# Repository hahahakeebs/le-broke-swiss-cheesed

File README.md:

I saw le broke and said, wow, it'd be really nice with more holes.

none of this is tested, yolo this to jlc at your own risk. I'm not responsible for you burning six dollars or anything that follows from you burning those six dollars.

assuming it works, then there is hotswap compatibility with MX, Choc v1/2, and KS27/33.

upstream readme follows below.

silly wacky split-but-not-split adaptation of le chiffre.

ez to assemble, reversible pcb, face down n!n/pro micro (zmk only!!), requires diodes and 2 6x6 buttons.

WATCH YOUR DIODE ORIENTATION!!! IT MATTERS!

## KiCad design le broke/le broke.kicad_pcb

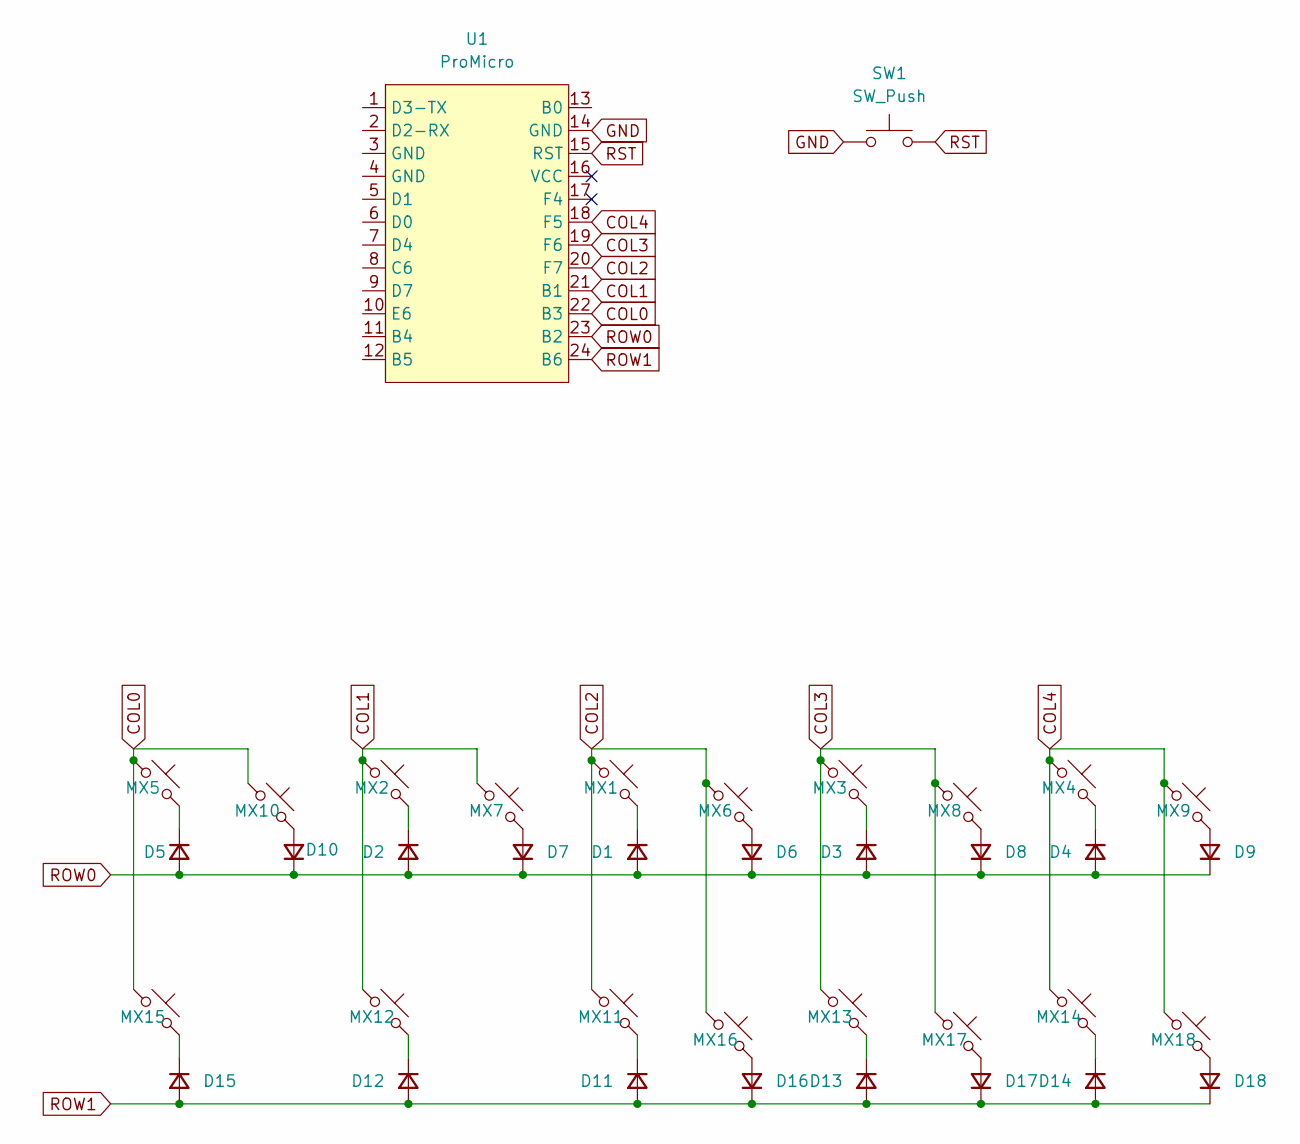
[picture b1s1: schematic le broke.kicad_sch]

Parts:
D1, D2, D3, D4, D5, D6, D7, D8, D9, D10, D11, D12, D13, D14, D15, D16, D17, D18: D_Small; D_A-405_P7.62mm_Horizontal
MX1, MX2, MX3, MX4, MX5, MX6, MX7, MX8, MX9, MX10, MX11, MX12, MX13, MX14, MX15, MX16, MX17, MX18: MX_SW_solder; SW_MX_1u_rev
SW1: SW_Push; SW_PUSH_6mm
U1: ProMicro; ProMicro_Reversible_Single

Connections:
COL0: MX5.1, MX10.1, MX15.1, U1.22 (B3)
COL1: MX2.1, MX7.1, MX12.1, U1.21 (B1)
COL2: MX1.1, MX6.1, MX11.1, MX16.1, U1.20 (F7)
COL3: MX3.1, MX8.1, MX13.1, MX17.1, U1.19 (F6)
COL4: MX4.1, MX9.1, MX14.1, MX18.1, U1.18 (F5)
GND: SW1.1, U1.14 (GND)
unnamed: D1.1 (K), MX1.2
unnamed: D2.1 (K), MX2.2
unnamed: D3.1 (K), MX3.2
unnamed: D4.1 (K), MX4.2
unnamed: D5.1 (K), MX5.2
unnamed: D6.2 (A), MX6.2
unnamed: D7.2 (A), MX7.2
unnamed: D8.2 (A), MX8.2
unnamed: D9.2 (A), MX9.2
unnamed: D10.2 (A), MX10.2
unnamed: D11.1 (K), MX11.2
unnamed: D12.1 (K), MX12.2
unnamed: D13.1 (K), MX13.2
unnamed: D14.1 (K), MX14.2
unnamed: D15.1 (K), MX15.2
unnamed: D16.2 (A), MX16.2
unnamed: D17.2 (A), MX17.2
unnamed: D18.2 (A), MX18.2
ROW0: D1.2 (A), D2.2 (A), D3.2 (A), D4.2 (A), D5.2 (A), D6.1 (K), D7.1 (K), D8.1 (K), D9.1 (K), D10.1 (K), U1.23 (B2)
ROW1: D11.2 (A), D12.2 (A), D13.2 (A), D14.2 (A), D15.2 (A), D16.1 (K), D17.1 (K), D18.1 (K), U1.24 (B6)
RST: SW1.2, U1.15 (RST)

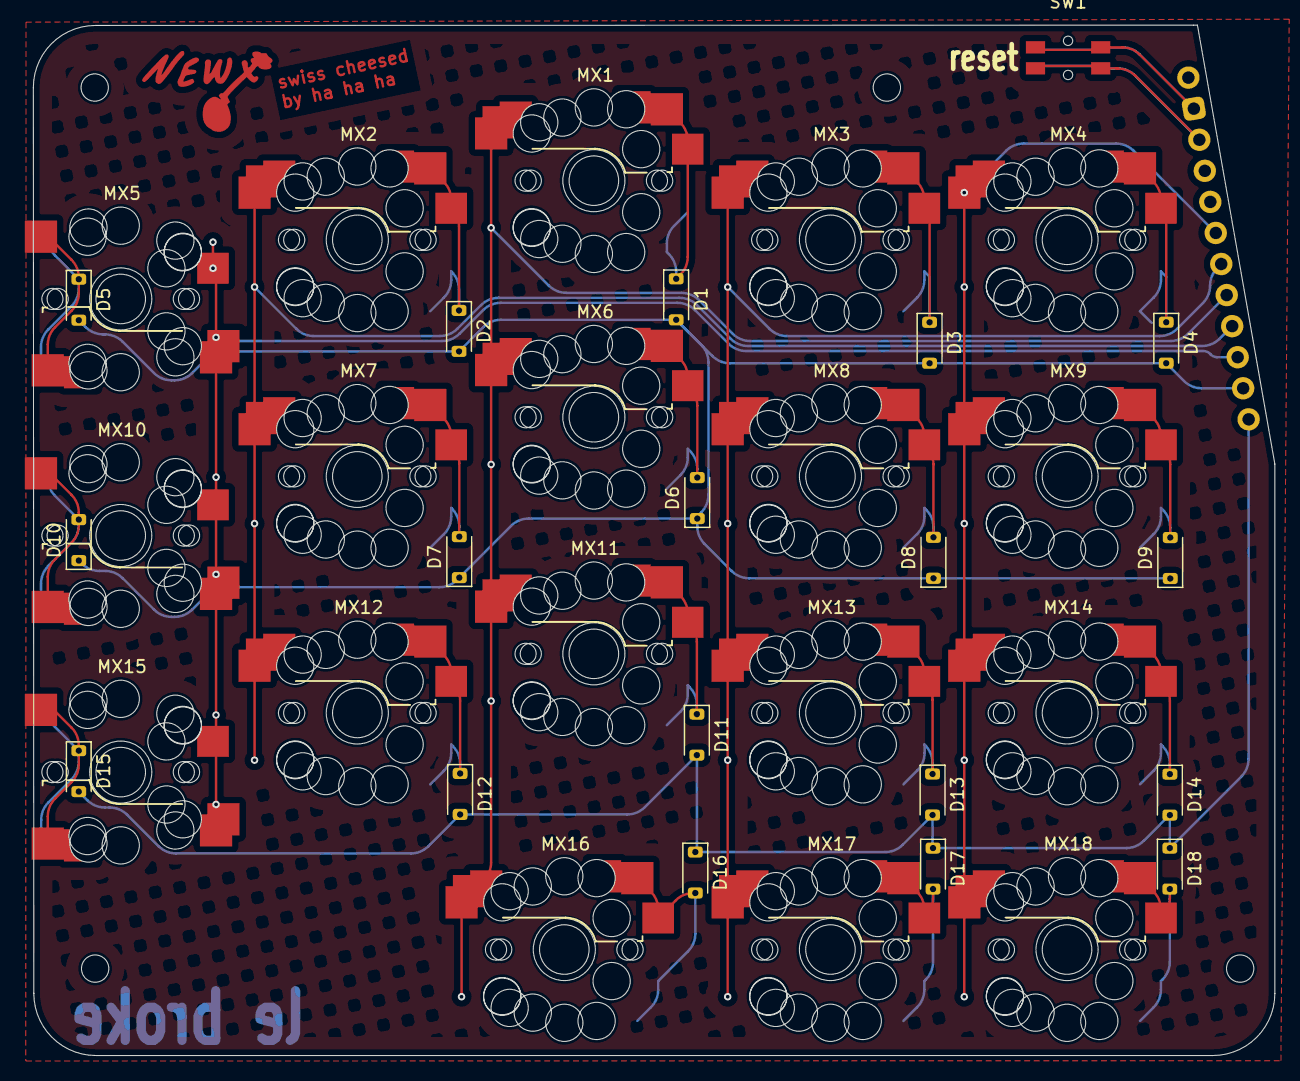
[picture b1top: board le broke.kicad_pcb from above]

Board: 2 copper layers, 100.0 x 83.0 mm, 38 parts (1 on the bottom side), 27 nets.

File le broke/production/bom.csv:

Designator,Footprint,Quantity,Value,LCSC Part #
"D1, D10, D11, D12, D13, D14, D15, D16, D17, D18, D2, D3, D4, D5, D6, D7, D8, D9",D_SOD-123,18,D_Small,
"MX1, MX11, MX12, MX13, MX14, MX16, MX17, MX18, MX2, MX3, MX4, MX6, MX7, MX8, MX9",gateron-ks27-choc-v1-mx-hotswap-reversible,15,MX_SW_solder,
"MX10, MX15, MX5",gateron-ks27-choc-v1-mx-hotswap-reversible edge preferred,3,MX_SW_solder,
SW1,Panasonic_EVQPUL_EVQPUC PTH,1,SW_Push,

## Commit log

2025-07-11 new pcb etc
2025-07-19 add pic and readme update
2025-08-25 firmware updates, file renaming
